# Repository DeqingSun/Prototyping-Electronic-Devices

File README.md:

# Prototyping Electronic Devices

ITPG-GT 2845 | 4 units | Fall 2020
Tuesday 4-6 over Zoom

Deqing Sun (deqing.sun[at]nyu.edu)

The most difficult part of prototyping is not the building process, but the process of deciding how to build. If we choose proper technology for prototypes, we can improve their robustness and simplicity.

This course will cover available and affordable technologies for ITP students to build prototypes. The course will start from soldering, wiring and LED basics. Then it extends to multitasking, signal processing, communication and advanced skills beyond PCom class.

Each session will have lectures followed by in class practices with guidance. Workshop sessions during midterm and final period allow students to work on their own project with help from instructors. No required assignment.

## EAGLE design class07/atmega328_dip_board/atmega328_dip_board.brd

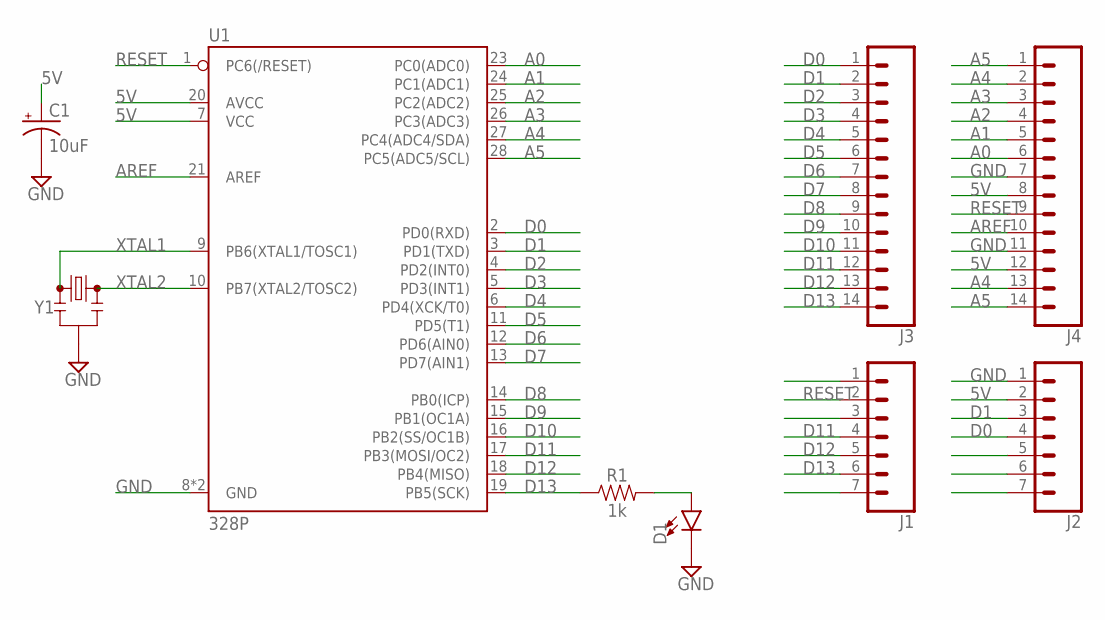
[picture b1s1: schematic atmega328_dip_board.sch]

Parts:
C1: 10uF; CPOL-RADIAL-2.5MM-5MM
D1: LED5MM; LED_5MM
J1, J2: CONN_07NO_SILK; 1X07_NO_SILK
J3, J4: CONN_14NO_SILK; 1X14_NO_SILK
R1: 1k; AXIAL-0.3
U1: 328P; DIP28
Y1: RESONATORPTH-7.6X3.8; RESONATOR-PTH-7.6X3.8

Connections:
5V: C1.1 (+), J2.2, J4.8, J4.12, U1.7 (VCC), U1.20 (AVCC)
A0: J4.6, U1.23 (PC0(ADC0))
A1: J4.5, U1.24 (PC1(ADC1))
A2: J4.4, U1.25 (PC2(ADC2))
A3: J4.3, U1.26 (PC3(ADC3))
A4: J4.2, J4.13, U1.27 (PC4(ADC4/SDA))
A5: J4.1, J4.14, U1.28 (PC5(ADC5/SCL))
AREF: J4.10, U1.21 (AREF)
D0: J2.4, J3.1, U1.2 (PD0(RXD))
D1: J2.3, J3.2, U1.3 (PD1(TXD))
D2: J3.3, U1.4 (PD2(INT0))
D3: J3.4, U1.5 (PD3(INT1))
D4: J3.5, U1.6 (PD4(XCK/T0))
D5: J3.6, U1.11 (PD5(T1))
D6: J3.7, U1.12 (PD6(AIN0))
D7: J3.8, U1.13 (PD7(AIN1))
D8: J3.9, U1.14 (PB0(ICP))
D9: J3.10, U1.15 (PB1(OC1A))
D10: J3.11, U1.16 (PB2(SS/OC1B))
D11: J1.4, J3.12, U1.17 (PB3(MOSI/OC2))
D12: J1.5, J3.13, U1.18 (PB4(MISO))
D13: J1.6, J3.14, R1.P$1 (1), U1.19 (PB5(SCK))
GND: C1.2 (-), D1.K (C), J2.1, J4.7, J4.11, U1.8 (GND), U1.22 (GND), Y1.2
unnamed: D1.A, R1.P$2 (2)
RESET: J1.2, J4.9, U1.1 (PC6(/RESET))
XTAL1: U1.9 (PB6(XTAL1/TOSC1)), Y1.1
XTAL2: U1.10 (PB7(XTAL2/TOSC2)), Y1.3

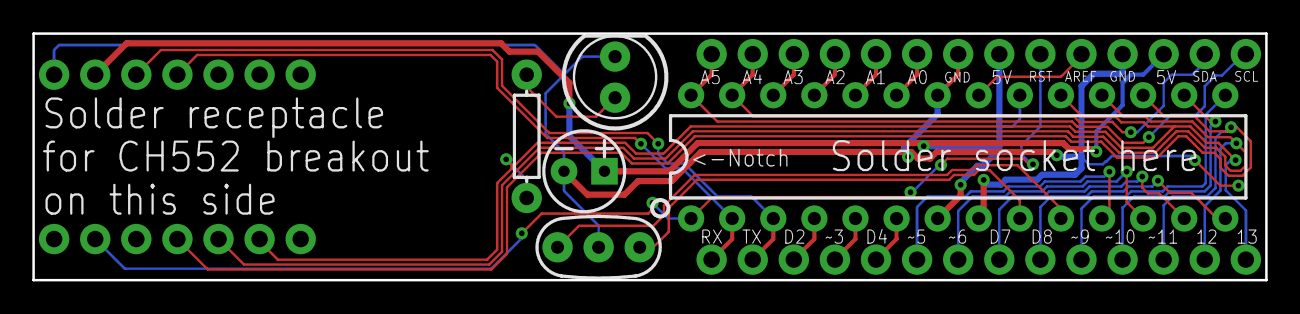
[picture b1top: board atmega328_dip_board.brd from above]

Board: 2 copper layers, 76.2 x 15.2 mm, 9 parts (0 on the bottom side), 27 nets.

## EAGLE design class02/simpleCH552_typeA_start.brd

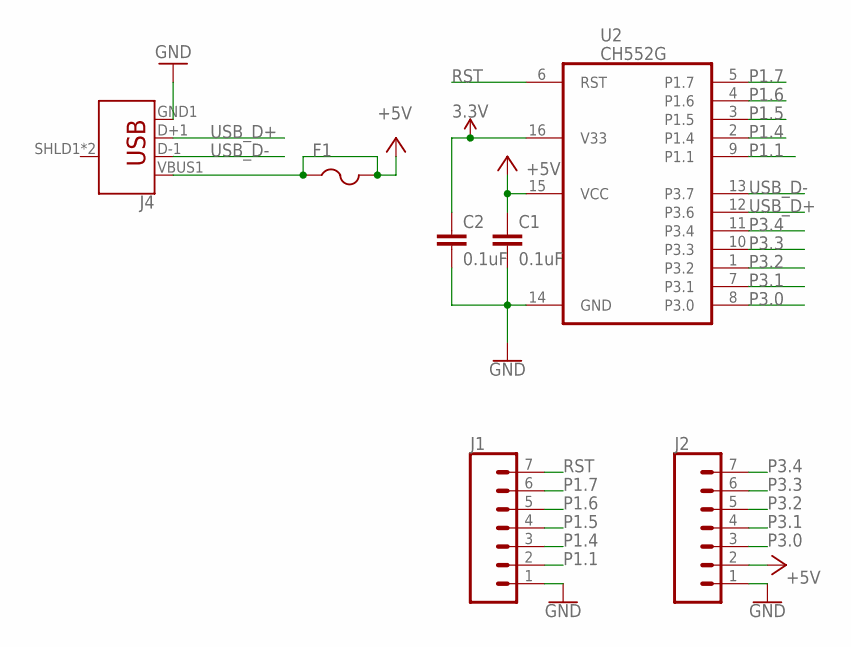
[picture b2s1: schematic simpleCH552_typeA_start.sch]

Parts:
C1, C2: 0.1uF; C0805K; LCSC C16834
F1: PTCFUSE-1206; R1206; LCSC C151162
J1, J2: CONN_07NO_SILK; 1X07_NO_SILK
J4: USB_A_SMT_MALE; USB-A-SMT-MALE
U2: CH552G; MY_IC_SO16; LCSC C111292

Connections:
3.3V: C2.1, U2.16 (V33)
+5V: C1.1, F1.1, F1.2, J2.2, J4.VBUS1 (VBUS), U2.15 (VCC)
GND: C1.2, C2.2, J1.1, J2.1, J4.GND1 (GND), U2.14 (GND)
P1.1: J1.2, U2.9 (P1.1)
P1.4: J1.3, U2.2 (P1.4)
P1.5: J1.4, U2.3 (P1.5)
P1.6: J1.5, U2.4 (P1.6)
P1.7: J1.6, U2.5 (P1.7)
P3.0: J2.3, U2.8 (P3.0)
P3.1: J2.4, U2.7 (P3.1)
P3.2: J2.5, U2.1 (P3.2)
P3.3: J2.6, U2.10 (P3.3)
P3.4: J2.7, U2.11 (P3.4)
RST: J1.7, U2.6 (RST)
USB_D+: J4.D+1 (D+), U2.12 (P3.6)
USB_D-: J4.D-1 (D-), U2.13 (P3.7)

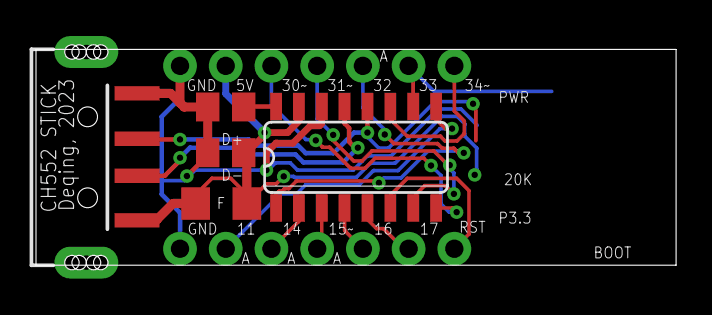
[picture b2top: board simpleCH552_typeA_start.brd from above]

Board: 2 copper layers, 35.6 x 12.0 mm, 7 parts (0 on the bottom side), 16 nets.

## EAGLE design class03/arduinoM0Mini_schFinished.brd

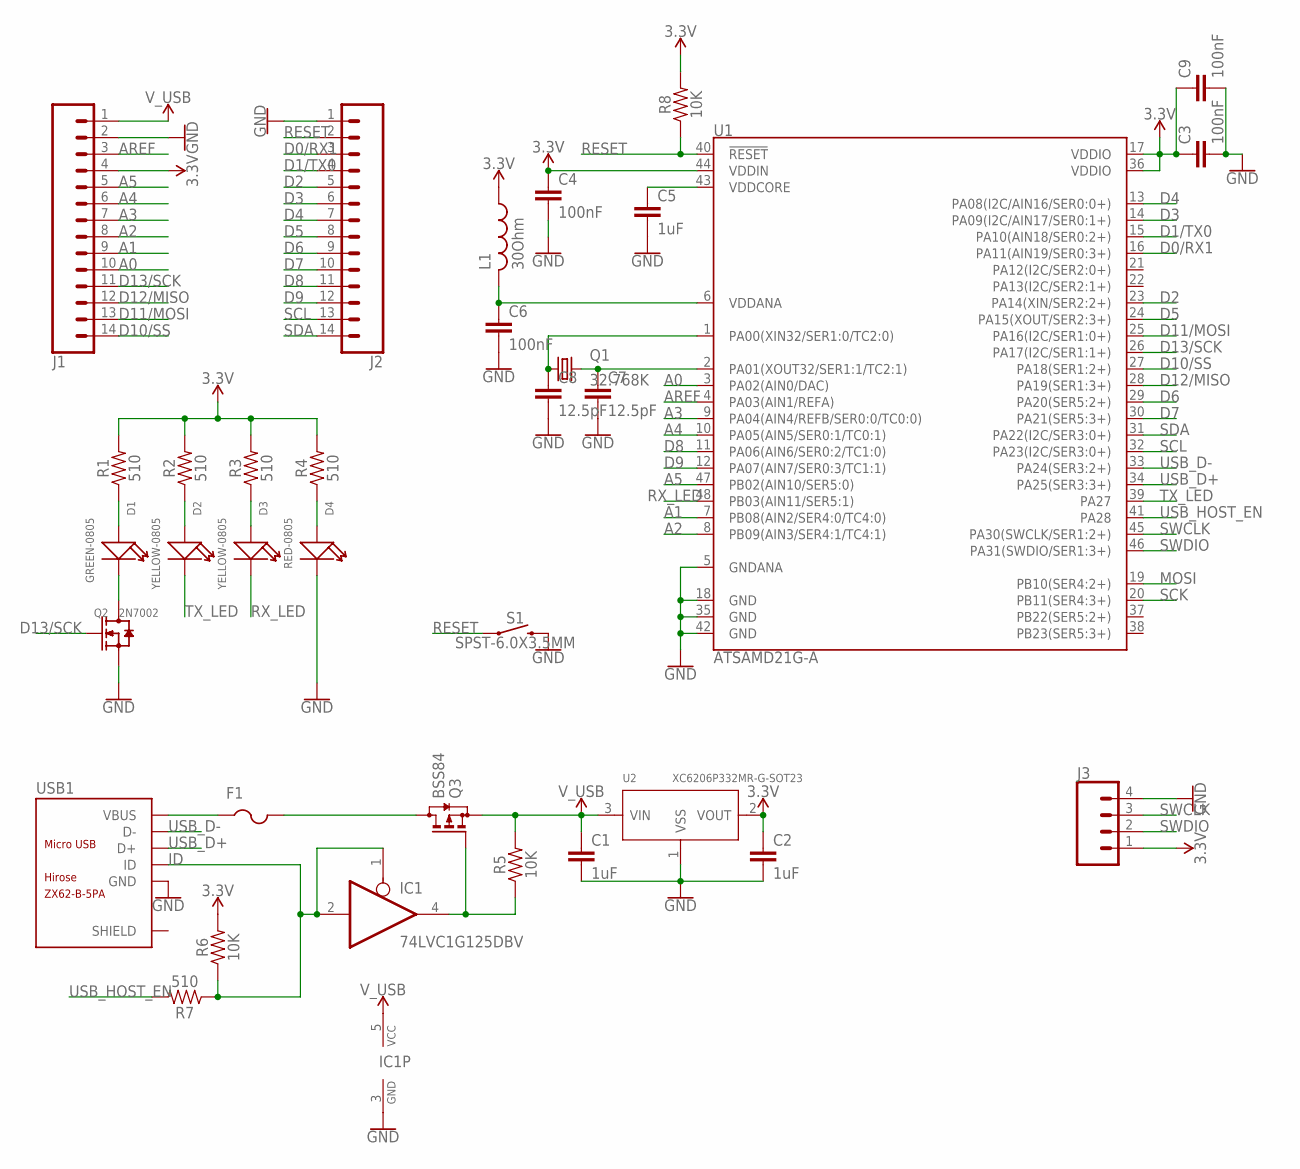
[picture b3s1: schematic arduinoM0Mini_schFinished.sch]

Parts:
C1, C2, C5: 1uF; C0805K; LCSC C16834
C3, C4, C6, C9: 100nF; C0805K; LCSC C1711
C7, C8: 12.5pF; C0805K; LCSC C1792
D1: GREEN-0805; LED-0805
D2, D3: YELLOW-0805; LED-0805
D4: RED-0805; LED-0805
F1: PTCFUSE-1206; R1206; LCSC C151162
IC1: 74LVC1G125DBV; SOT23-5; LCSC C23654
J1, J2: CONN_14NO_SILK; 1X14_NO_SILK
J3: CONN_04LOCK_LONGPADS; 1X04_LOCK_LONGPADS
L1: 30Ohm; RESC0805_N; LCSC C139190
Q1: 32.768K; 3.2X1.5; LCSC C32346
Q2: 2N7002; SOT-23
Q3: BSS84; SOT23; LCSC C8492
R1, R2, R3, R4: 510; 0805
R5, R6, R8: 10K; 0805; LCSC C115309
R7: 510; 0805; LCSC C17734
S1: SPST-6.0X3.5MM; TACTILE_SWITCH_SMD_6.0X3.5MM; LCSC C139783
U1: ATSAMD21G-A; TQFP-48
U2: XC6206P332MR-G-SOT23; SOT-23; LCSC C5446
USB1: ZX62-B-5PA; MICRO-USB5+6P-SMD-0.65-AB; LCSC C10418

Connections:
3.3V: C2.1, C3.1, C4.1, C9.1, J1.4, J3.1, L1.1, R1.2, R2.2, R3.2, R4.2, R6.2, R8.2, U1.17 (VDDIO), U1.36 (VDDIO), U1.44 (VDDIN), U2.2 (VOUT)
A0: J1.10, U1.3 (PA02(AIN0/DAC))
A1: J1.9, U1.7 (PB08(AIN2/SER4:0/TC4:0))
A2: J1.8, U1.8 (PB09(AIN3/SER4:1/TC4:1))
A3: J1.7, U1.9 (PA04(AIN4/REFB/SER0:0/TC0:0))
A4: J1.6, U1.10 (PA05(AIN5/SER0:1/TC0:1))
A5: J1.5, U1.47 (PB02(AIN10/SER5:0))
AREF: J1.3, U1.4 (PA03(AIN1/REFA))
D0/RX1: J2.3, U1.16 (PA11(AIN19/SER0:3+))
D1/TX0: J2.4, U1.15 (PA10(AIN18/SER0:2+))
D2: J2.5, U1.23 (PA14(XIN/SER2:2+))
D3: J2.6, U1.14 (PA09(I2C/AIN17/SER0:1+))
D4: J2.7, U1.13 (PA08(I2C/AIN16/SER0:0+))
D5: J2.8, U1.24 (PA15(XOUT/SER2:3+))
D6: J2.9, U1.29 (PA20(SER5:2+))
D7: J2.10, U1.30 (PA21(SER5:3+))
D8: J2.11, U1.11 (PA06(AIN6/SER0:2/TC1:0))
D9: J2.12, U1.12 (PA07(AIN7/SER0:3/TC1:1))
D10/SS: J1.14, U1.27 (PA18(SER1:2+))
D11/MOSI: J1.13, U1.25 (PA16(I2C/SER1:0+))
D12/MISO: J1.12, U1.28 (PA19(SER1:3+))
D13/SCK: J1.11, Q2.1 (G), U1.26 (PA17(I2C/SER1:1+))
GND: C1.2, C2.2, C3.2, C4.2, C5.2, C6.2, C7.2, C8.2, C9.2, D4.-, IC1.3 (GND), J1.2, J2.1, J3.4, Q2.2 (S), S1.2, U1.5 (GNDANA), U1.18 (GND), U1.35 (GND), U1.42 (GND), U2.1 (VSS), USB1.5 (GND)
ID: IC1.1 (OE), IC1.2 (I), R6.1, R7.1, USB1.4 (ID)
MOSI: U1.19 (PB10(SER4:2+))
unnamed: D1.+, R1.1
unnamed: D2.+, R2.1
unnamed: C7.1, Q1.2, U1.2 (PA01(XOUT32/SER1:1/TC2:1))
unnamed: C8.1, Q1.1, U1.1 (PA00(XIN32/SER1:0/TC2:0))
unnamed: D3.+, R3.1
unnamed: D4.+, R4.1
unnamed: D1.-, Q2.3 (D)
unnamed: IC1.4 (O), Q3.1 (G), R5.1
unnamed: F1.2, Q3.3 (D)
RESET: J2.2, R8.1, S1.1, U1.40 (!RESET!)
RX_LED: D3.-, U1.48 (PB03(AIN11/SER5:1))
SCK: U1.20 (PB11(SER4:3+))
SCL: J2.13, U1.32 (PA23(I2C/SER3:0+))
SDA: J2.14, U1.31 (PA22(I2C/SER3:0+))
SWCLK: J3.3, U1.45 (PA30(SWCLK/SER1:2+))
SWDIO: J3.2, U1.46 (PA31(SWDIO/SER1:3+))
TX_LED: D2.-, U1.39 (PA27)
USB_D+: U1.34 (PA25(SER3:3+)), USB1.3 (D+)
USB_D-: U1.33 (PA24(SER3:2+)), USB1.2 (D-)
USB_HOST_EN: R7.2, U1.41 (PA28)
VDDADA: C6.1, L1.2, U1.6 (VDDANA)
VDDCORE: C5.1, U1.43 (VDDCORE)
V_USB: C1.1, IC1.5 (VCC), J1.1, Q3.2 (S), R5.2, U2.3 (VIN)
V_USB_IN: F1.1, USB1.1 (VBUS)

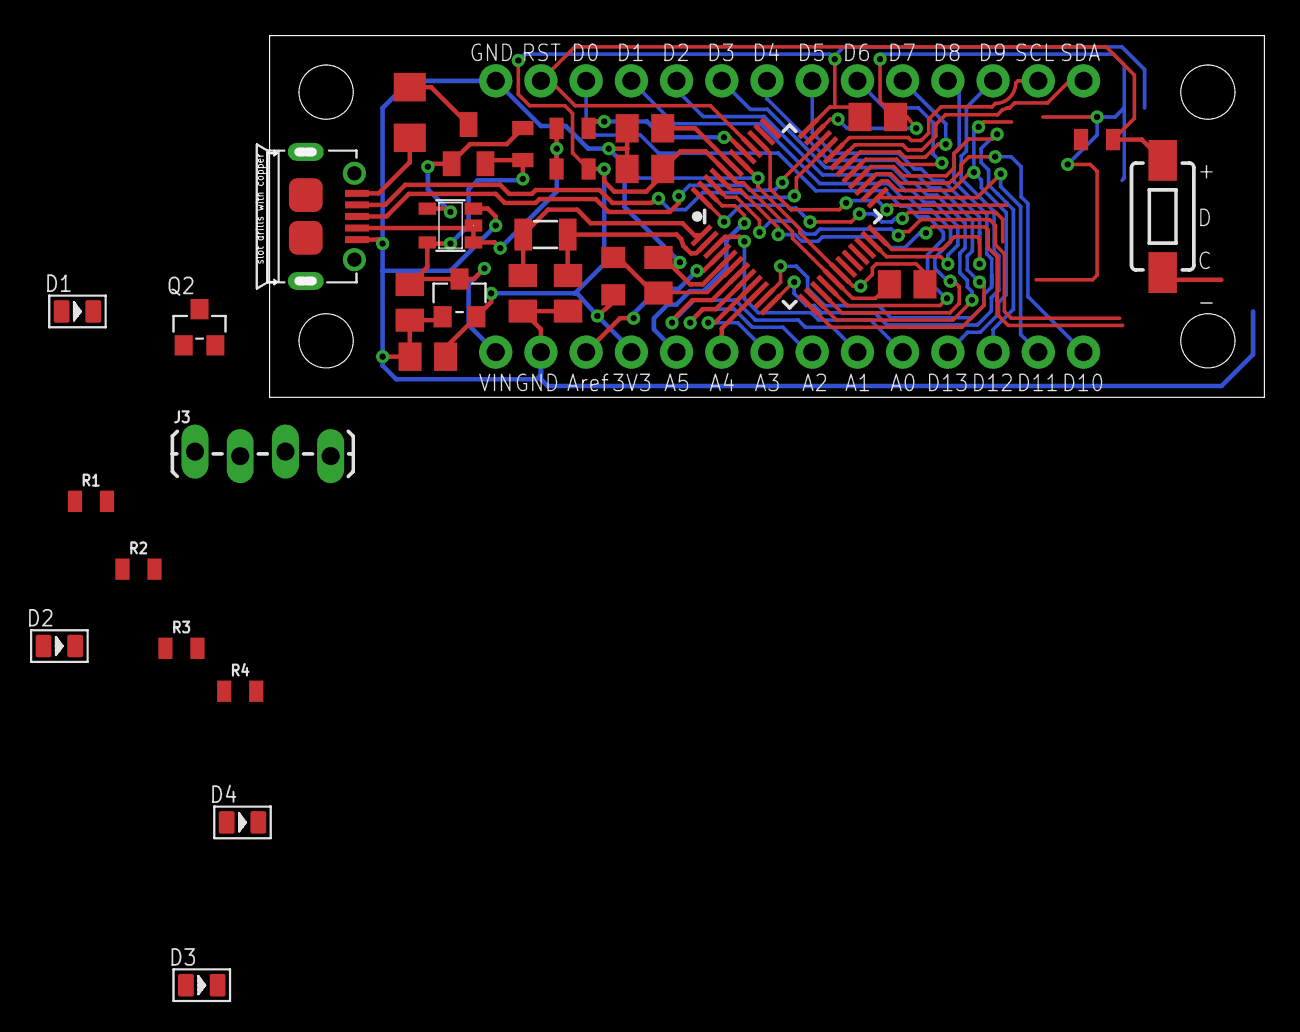
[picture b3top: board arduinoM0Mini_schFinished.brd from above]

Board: 2 copper layers, 55.9 x 20.3 mm, 34 parts (0 on the bottom side), 47 nets.

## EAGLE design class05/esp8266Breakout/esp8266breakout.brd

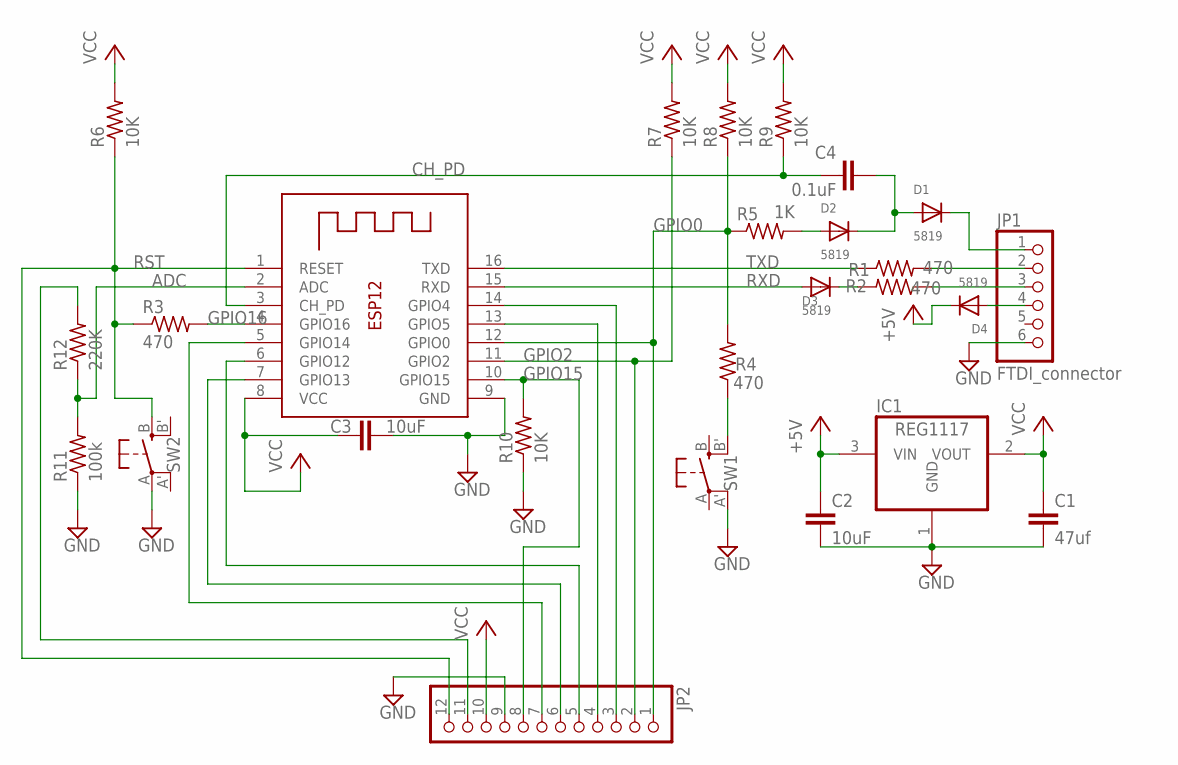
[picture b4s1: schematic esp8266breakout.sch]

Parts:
C1: 47uf; C1206K
C2, C3: 10uF; C0805K
C4: 0.1uF; C0805K
D1, D2, D3, D4: 5819; SOD-123
IC1: REG1117; SOT223
JP1: FTDI_connector; 1X06-BIGLOCK
JP2: PINHD-1X12/90; 1X12/90
R1, R2, R3, R4: 470; R0805
R5: 1K; R0805
R6, R7, R8, R9, R10: 10K; R0805
R11: 100k; R0805
R12: 220K; R0805
SW1, SW2: 6*6mm; EVQ-Q2
X1: ESP_12S; ESP-12

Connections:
+5V: C2.1, D4.C, IC1.3 (VIN)
ADC: R11.2, R12.1, X1.2 (ADC)
ADC_EXT: JP2.11, R12.2
CH_PD: C4.1, R9.1, X1.3 (CH_PD)
DTR: D1.C, JP1.1
GND: C1.2, C2.2, C3.2, IC1.1 (GND), JP1.6, JP2.9, R10.1, R11.1, SW1.A' (P1), SW2.A, X1.9 (GND)
GPIO0: JP2.1, R4.2, R5.1, R8.1, X1.12 (GPIO0)
GPIO2: JP2.2, R7.1, X1.11 (GPIO2)
GPIO4: JP2.3, X1.14 (GPIO4)
GPIO5: JP2.4, X1.13 (GPIO5)
GPIO12: JP2.5, X1.6 (GPIO12)
GPIO13: JP2.6, X1.7 (GPIO13)
GPIO14: JP2.7, X1.5 (GPIO14)
GPIO15: JP2.8, R10.2, X1.10 (GPIO15)
GPIO16: R3.2, X1.4 (GPIO16)
unnamed: R4.1, SW1.B' (S1)
unnamed: C4.2, D1.A, D2.C
unnamed: D2.A, R5.2
unnamed: D3.C, R2.2
RST: JP2.12, R3.1, R6.1, SW2.B (S), X1.1 (RESET)
RXD: D3.A, X1.15 (RXD)
RXD_EXT: JP1.3, R2.1
TXD: R1.1, X1.16 (TXD)
TXD_EXT: JP1.2, R1.2
VCC: C1.1, C3.1, IC1.2 (VOUT), JP2.10, R6.2, R7.2, R8.2, R9.2, X1.8 (VCC)
VIN: D4.A, JP1.4

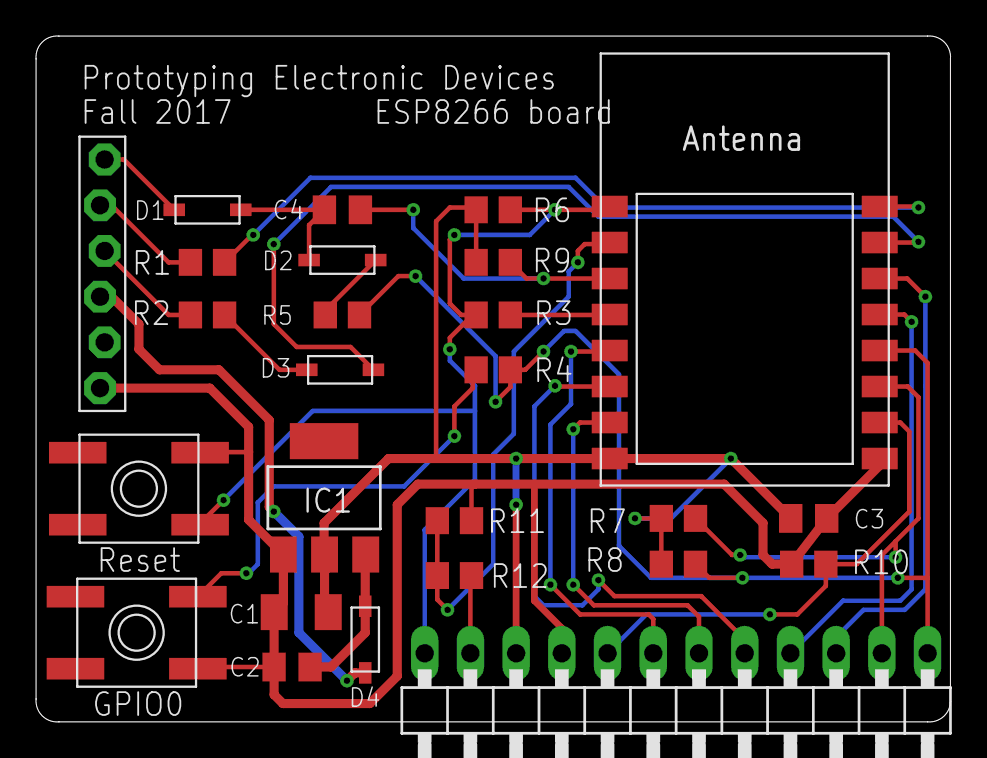
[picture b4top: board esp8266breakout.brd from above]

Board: 2 copper layers, 50.8 x 38.1 mm, 26 parts (0 on the bottom side), 26 nets.

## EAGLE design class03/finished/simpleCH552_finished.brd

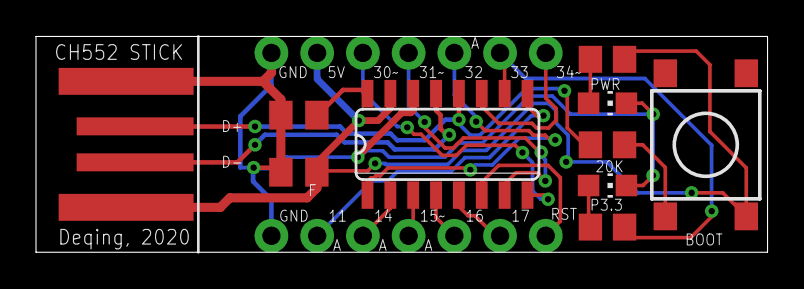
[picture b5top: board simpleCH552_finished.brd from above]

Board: 2 copper layers, 40.6 x 12.0 mm, 12 parts (0 on the bottom side), 19 nets.

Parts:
C1, C2: 0.1uF; C0805K
J1, J2: 1X07_NO_SILK
LED1: RED; CHIP-LED0805
LED2: GREEN; CHIP-LED0805
R1, R2, R3: 20K; R0805
S1: MOMENTARY-SWITCH-SPST-SMD-6.2MM-TALL; TACTILE_SWITCH_SMD_6.2MM_TALL
U1: CH552G; MY_IC_SO16
X1: USBPCB; USB-A-PCB

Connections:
3.3V: C2.1, U1.16
+5V: C1.1, J2.2, R2.1, S1.B2, U1.15, X1.5V
GND: C1.2, C2.2, J1.1, J2.1, LED1.C, LED2.C, U1.14, X1.GND
unnamed: R1.2, S1.A2
unnamed: LED1.A, R2.2
unnamed: LED2.A, R3.2
P1.1: J1.2, U1.9
P1.4: J1.3, U1.2
P1.5: J1.4, U1.3
P1.6: J1.5, U1.4
P1.7: J1.6, U1.5
P3.0: J2.3, U1.8
P3.1: J2.4, U1.7
P3.2: J2.5, U1.1
P3.3: J2.6, R3.1, U1.10
P3.4: J2.7, U1.11
RST: J1.7, U1.6
USB_D+: R1.1, U1.12, X1.USB_P
USB_D-: U1.13, X1.USB_M

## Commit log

2016-01-27 add led code
2016-02-02 add example for class 2
2016-02-02 add img
2016-02-11 add code for class 3
2016-02-19 add code class04
2016-03-03 add gerber and BOM
2016-03-10 add class 07 code
2016-03-10 remove comment
2016-03-10 use high low byte function
2016-03-10 add ADXL345 arduino
2016-04-06 Create gh-pages branch via GitHub
2016-04-06 Added files via upload
2016-04-07 add example
2016-04-14 add class 11
2016-04-15 update tap
    kind of work
2016-04-25 update class
2016-04-26 add Notify
2017-09-11 add code for class 2
2017-09-18 add slow switch
2017-09-18 add cube example
2017-09-18 update code
2017-09-19 add neopixel
2017-09-26 add control
2017-09-26 add code
2017-09-26 add local example
2017-09-27 add link
2017-10-02 add eagle file
2017-10-09 add class rule
2017-10-17 remove old file
2017-10-17 add cam
2017-11-23 add htmlPage
2018-09-16 add finished file
2018-09-16 add start board
2018-09-17 add ADD parts
2018-09-17 add ADD bom
2018-09-22 add sch finished version
2018-09-22 add command to copy
2018-10-01 add class 04 code
2018-10-09 add sketches
2018-10-27 add blink example
2018-10-27 replace home path
2018-10-27 add nop
2018-10-28 add debug example
2018-10-28 add ledClass
2018-10-28 add debug2
2018-11-19 add sketch
2018-11-25 add i2c example
2018-11-25 add request
2018-11-25 add schematic
2018-12-02 add class 13 material
2019-09-24 rename rule file and add cam file
2019-11-18 add drv8825 demo
2020-09-09 remove all old content for now
2020-09-09 add finished PCB
2020-09-10 update part number
2020-09-11 move parts
2020-09-12 remove DNP
2020-09-12 remove fuse and test point
2020-09-12 create start schematic
2020-09-12 add part list
2020-09-12 update list
2020-09-19 add sch finished file
2020-09-26 add class4 content
2020-10-01 add class 5
2020-10-10 add class06
2020-10-25 add class 09
2020-10-27 add more sleep examples
2020-10-28 change file name
2020-10-29 add pin detection
2020-10-29 update datatype
2020-10-29 change name
2020-11-03 add p5js debug
2020-11-06 add blinkUno
2020-11-06 update dwdebug
2020-11-08 add exercise
2020-11-08 add logic analogwrite
2020-11-11 use static link version
2020-11-16 add demo
2020-11-22 add example 1 and 2
2020-11-22 add example 3&4
2022-09-08 update to USB shell model
2022-10-18 update example
2023-09-10 update ibeacon scanner
2023-09-10 replace finished with typeA connector
2023-09-10 change sch finished
2023-09-10 change start
2024-08-12 start to work on dip board
2024-08-13 update board
2024-10-18 update firmware
2025-09-05 change finished PCB to easyeda
2025-09-05 change start to easyeda
2025-09-05 remove needed part
2025-09-08 add sch finished
2025-09-08 remove outline on connector
2025-09-09 remove btm trace
2025-10-23 add ch571 example
2025-11-13 add hex and flash script

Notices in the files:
parts and their libraries:
SparkFun-Connectors: Licensing: Creative Commons ShareAlike 4.0 International - https://creativecommons.org/licenses/by-sa/4.0
SparkFun: Licensing: CC v3.0 Share-Alike You are welcome to use this library for commercial purposes.
crystal-geyer_V1_0: Copyright: Geyer-Electronic
